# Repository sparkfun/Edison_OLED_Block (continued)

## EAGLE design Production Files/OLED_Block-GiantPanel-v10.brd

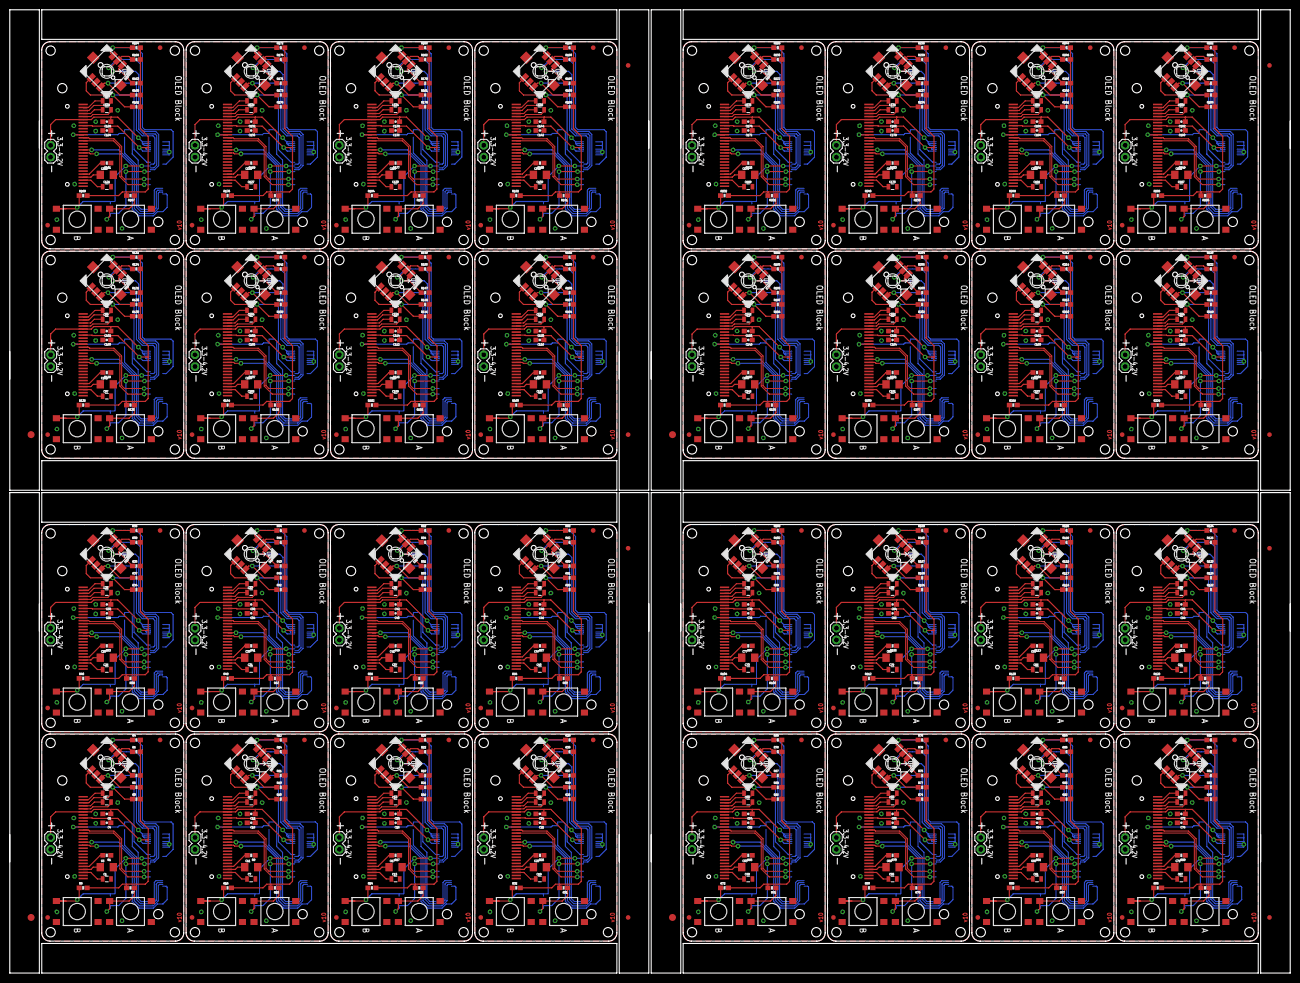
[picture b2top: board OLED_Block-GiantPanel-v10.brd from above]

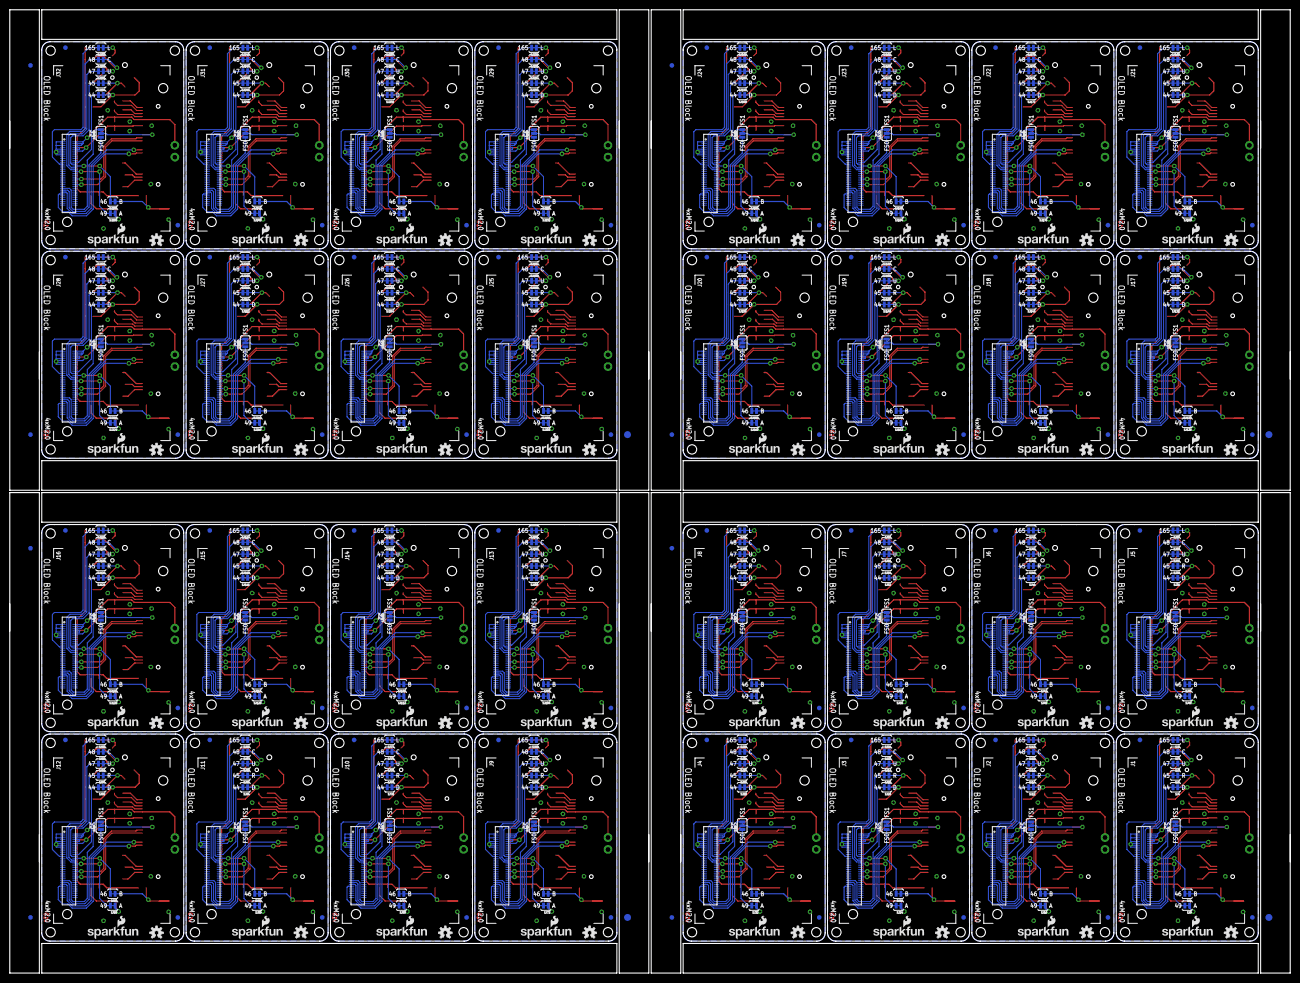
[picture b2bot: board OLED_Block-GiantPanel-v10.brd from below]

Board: 2 copper layers, 274.8 x 206.8 mm, 1112 parts (428 on the bottom side), 1024 nets.

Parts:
C1, C7, C13, C19, C25, C31, C37, C43, C49, C55, C61, C67, C73, C79, C85, C91, C97, C103, C109, C115, C121, C127, C133, C139, C145, C151, C157, C163, C169, C175, C181, C187: 2.2uF; 0805
C2, C3, C8, C9, C14, C15, C20, C21, C26, C27, C32, C33, C38, C39, C44, C45, C50, C51, C56, C57, C62, C63, C68, C69, C74, C75, C80, C81, C86, C87, C92, C93, C98, C99, C104, C105, C110, C111, C116, C117, C122, C123, C128, C129, C134, C135, C140, C141, C146, C147, C152, C153, C158, C159, C164, C165, C170, C171, C176, C177, C182, C183, C188, C189: 1uF X5R; 0805
C4, C6, C10, C12, C16, C18, C22, C24, C28, C30, C34, C36, C40, C42, C46, C48, C52, C54, C58, C60, C64, C66, C70, C72, C76, C78, C82, C84, C88, C90, C94, C96, C100, C102, C106, C108, C112, C114, C118, C120, C124, C126, C130, C132, C136, C138, C142, C144, C148, C150, C154, C156, C160, C162, C166, C168, C172, C174, C178, C180, C184, C186, C190, C192: 1uF; 0603-CAP
C5, C11, C17, C23, C29, C35, C41, C47, C53, C59, C65, C71, C77, C83, C89, C95, C101, C107, C113, C119, C125, C131, C137, C143, C149, C155, C161, C167, C173, C179, C185, C191: 4.7uF/16V; 1206
E$1, E$2, E$9, E$10, E$15, E$16, E$21, E$22: FIDUCIAL-1.5X3
E$3, E$4, E$5, E$6, E$7, E$8, E$11, E$12, E$13, E$14, E$17, E$18, E$19, E$20, E$23, E$24: FIDUCIAL-1X2
FID1, FID2, FID3, FID4, FID5, FID6, FID7, FID8, FID9, FID10, FID11, FID12, FID13, FID14, FID15, FID16, FID17, FID18, FID19, FID20, FID21, FID22, FID23, FID24, FID25, FID26, FID27, FID28, FID29, FID30, FID31, FID32, FID33, FID34, FID35, FID36, FID37, FID38, FID39, FID40, FID41, FID42, FID43, FID44, FID45, FID46, FID47, FID48, FID49, FID50, FID51, FID52, FID53, FID54, FID55, FID56, FID57, FID58, FID59, FID60, FID61, FID62, FID63, FID64, FID65, FID66, FID67, FID68, FID69, FID70, FID71, FID72, FID73, FID74, FID75, FID76, FID77, FID78, FID79, FID80, FID81, FID82, FID83, FID84, FID85, FID86, FID87, FID88, FID89, FID90, FID91, FID92, FID93, FID94, FID95, FID96, FID97, FID98, FID99, FID100, FID101, FID102, FID103, FID104, FID105, FID106, FID107, FID108, FID109, FID110, FID111, FID112, FID113, FID114, FID115, FID116, FID117, FID118, FID119, FID120, FID121, FID122, FID123, FID124, FID125, FID126, FID127, FID128: FIDUCIAL1X2; FIDUCIAL-1X2
J1, J2, J3, J4, J5, J6, J7, J8, J9, J10, J11, J12, J13, J14, J15, J16, J17, J18, J19, J20, J21, J22, J23, J24, J25, J26, J27, J28, J29, J30, J31, J32: EDISON_CONNECTOR_FULLMOUNTING_HOLES; EDISON_DAUGHTER
JP1, JP2, JP3, JP4, JP5, JP6, JP7, JP8, JP9, JP10, JP11, JP12, JP13, JP14, JP15, JP16, JP17, JP18, JP19, JP20, JP21, JP22, JP23, JP24, JP25, JP26, JP27, JP28, JP29, JP30, JP31, JP32: M02PTH; 1X02
LOGO1, LOGO2, LOGO5, LOGO7, LOGO9, LOGO11, LOGO13, LOGO15, LOGO17, LOGO19, LOGO21, LOGO23, LOGO25, LOGO27, LOGO29, LOGO31, LOGO33, LOGO35, LOGO37, LOGO39, LOGO41, LOGO43, LOGO45, LOGO47, LOGO49, LOGO51, LOGO53, LOGO55, LOGO57, LOGO59, LOGO61, LOGO63: OSHW-LOGOS; OSHW-LOGO-S
LOGO3, LOGO4, LOGO6, LOGO8, LOGO10, LOGO12, LOGO14, LOGO16, LOGO18, LOGO20, LOGO22, LOGO24, LOGO26, LOGO28, LOGO30, LOGO32, LOGO34, LOGO36, LOGO38, LOGO40, LOGO42, LOGO44, LOGO46, LOGO48, LOGO50, LOGO52, LOGO54, LOGO56, LOGO58, LOGO60, LOGO62, LOGO64: SFE_LOGO_NAME_FLAME.1_INCH; SFE_LOGO_NAME_FLAME_.1
OLED1, OLED2, OLED3, OLED4, OLED5, OLED6, OLED7, OLED8, OLED9, OLED10, OLED11, OLED12, OLED13, OLED14, OLED15, OLED16, OLED17, OLED18, OLED19, OLED20, OLED21, OLED22, OLED23, OLED24, OLED25, OLED26, OLED27, OLED28, OLED29, OLED30, OLED31, OLED32: OLED0.66; OLED-0.66-64X48
R1, R9, R17, R25, R33, R41, R49, R57, R65, R73, R81, R89, R97, R105, R113, R121, R129, R137, R145, R153, R161, R169, R177, R185, R193, R201, R209, R217, R225, R233, R241, R249: 390k; 0603-RES
R2, R3, R4, R5, R6, R7, R8, R10, R11, R12, R13, R14, R15, R16, R18, R19, R20, R21, R22, R23, R24, R26, R27, R28, R29, R30, R31, R32, R34, R35, R36, R37, R38, R39, R40, R42, R43, R44, R45, R46, R47, R48, R50, R51, R52, R53, R54, R55, R56, R58, R59, R60, R61, R62, R63, R64, R66, R67, R68, R69, R70, R71, R72, R74, R75, R76, R77, R78, R79, R80, R82, R83, R84, R85, R86, R87, R88, R90, R91, R92, R93, R94, R95, R96, R98, R99, R100, R101, R102, R103, R104, R106, R107, R108, R109, R110, R111, R112, R114, R115, R116, R117, R118, R119, R120, R122, R123, R124, R125, R126, R127, R128, R130, R131, R132, R133, R134, R135, R136, R138, R139, R140, R141, R142, R143, R144, R146, R147, R148, R149, R150, R151, R152, R154, R155, R156, R157, R158, R159, R160, R162, R163, R164, R165, R166, R167, R168, R170, R171, R172, R173, R174, R175, R176, R178, R179, R180, R181, R182, R183, R184, R186, R187, R188, R189, R190, R191, R192, R194, R195, R196, R197, R198, R199, R200, R202, R203, R204, R205, R206, R207, R208, R210, R211, R212, R213, R214, R215, R216, R218, R219, R220, R221, R222, R223, R224, R226, R227, R228, R229, R230, R231, R232, R234, R235, R236, R237, R238, R239, R240, R242, R243, R244, R245, R246, R247, R248, R250, R251, R252, R253, R254, R255, R256: 10K; 0603-RES
S1, S4, S7, S10, S13, S16, S19, S22, S25, S28, S31, S34, S37, S40, S43, S46, S49, S52, S55, S58, S61, S64, S67, S70, S73, S76, S79, S82, S85, S88, S91, S94: Button A; TACTILE_SWITCH_TALL
S2, S5, S8, S11, S14, S17, S20, S23, S26, S29, S32, S35, S38, S41, S44, S47, S50, S53, S56, S59, S62, S65, S68, S71, S74, S77, S80, S83, S86, S89, S92, S95: Button B; TACTILE_SWITCH_TALL
S3, S6, S9, S12, S15, S18, S21, S24, S27, S30, S33, S36, S39, S42, S45, S48, S51, S54, S57, S60, S63, S66, S69, S72, S75, S78, S81, S84, S87, S90, S93, S96: JOYSTICK_MINI
SJ1, SJ3, SJ4, SJ5, SJ6, SJ7, SJ8, SJ10, SJ11, SJ12, SJ13, SJ14, SJ15, SJ16, SJ18, SJ19, SJ20, SJ21, SJ22, SJ23, SJ24, SJ26, SJ27, SJ28, SJ29, SJ30, SJ31, SJ32, SJ34, SJ35, SJ36, SJ37, SJ38, SJ39, SJ40, SJ42, SJ43, SJ44, SJ45, SJ46, SJ47, SJ48, SJ50, SJ51, SJ52, SJ53, SJ54, SJ55, SJ56, SJ58, SJ59, SJ60, SJ61, SJ62, SJ63, SJ64, SJ66, SJ67, SJ68, SJ69, SJ70, SJ71, SJ72, SJ74, SJ75, SJ76, SJ77, SJ78, SJ79, SJ80, SJ82, SJ83, SJ84, SJ85, SJ86, SJ87, SJ88, SJ90, SJ91, SJ92, SJ93, SJ94, SJ95, SJ96, SJ98, SJ99, SJ100, SJ101, SJ102, SJ103, SJ104, SJ106, SJ107, SJ108, SJ109, SJ110, SJ111, SJ112, SJ114, SJ115, SJ116, SJ117, SJ118, SJ119, SJ120, SJ122, SJ123, SJ124, SJ125, SJ126, SJ127, SJ128, SJ130, SJ131, SJ132, SJ133, SJ134, SJ135, SJ136, SJ138, SJ139, SJ140, SJ141, SJ142, SJ143, SJ144, SJ146, SJ147, SJ148, SJ149, SJ150, SJ151, SJ152, SJ154, SJ155, SJ156, SJ157, SJ158, SJ159, SJ160, SJ162, SJ163, SJ164, SJ165, SJ166, SJ167, SJ168, SJ170, SJ171, SJ172, SJ173, SJ174, SJ175, SJ176, SJ178, SJ179, SJ180, SJ181, SJ182, SJ183, SJ184, SJ186, SJ187, SJ188, SJ189, SJ190, SJ191, SJ192, SJ194, SJ195, SJ196, SJ197, SJ198, SJ199, SJ200, SJ202, SJ203, SJ204, SJ205, SJ206, SJ207, SJ208, SJ210, SJ211, SJ212, SJ213, SJ214, SJ215, SJ216, SJ218, SJ219, SJ220, SJ221, SJ222, SJ223, SJ224, SJ226, SJ227, SJ228, SJ229, SJ230, SJ231, SJ232, SJ234, SJ235, SJ236, SJ237, SJ238, SJ239, SJ240, SJ242, SJ243, SJ244, SJ245, SJ246, SJ247, SJ248, SJ250, SJ251, SJ252, SJ253, SJ254, SJ255, SJ256: PAD-JUMPER-2-NC_BY_TRACE_YES_SILK
SJ2, SJ9, SJ17, SJ25, SJ33, SJ41, SJ49, SJ57, SJ65, SJ73, SJ81, SJ89, SJ97, SJ105, SJ113, SJ121, SJ129, SJ137, SJ145, SJ153, SJ161, SJ169, SJ177, SJ185, SJ193, SJ201, SJ209, SJ217, SJ225, SJ233, SJ241, SJ249: CS_SEL; PAD-JUMPER-3-2OF3_NC_BY_TRACE_YES_SILK_FULL_BOX

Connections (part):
1.8V: C4.1, J1.12, OLED1.8, R2.2, R3.2, R4.2, R5.2, R6.2, R7.2, R8.2
1.8V1: C10.1, J2.12, OLED2.8, R10.2, R11.2, R12.2, R13.2, R14.2, R15.2, R16.2
1.8V2: C16.1, J3.12, OLED3.8, R18.2, R19.2, R20.2, R21.2, R22.2, R23.2, R24.2
1.8V3: C22.1, J4.12, OLED4.8, R26.2, R27.2, R28.2, R29.2, R30.2, R31.2, R32.2
1.8V4: C28.1, J5.12, OLED5.8, R34.2, R35.2, R36.2, R37.2, R38.2, R39.2, R40.2
1.8V5: C34.1, J6.12, OLED6.8, R42.2, R43.2, R44.2, R45.2, R46.2, R47.2, R48.2
1.8V6: C40.1, J7.12, OLED7.8, R50.2, R51.2, R52.2, R53.2, R54.2, R55.2, R56.2
1.8V7: C46.1, J8.12, OLED8.8, R58.2, R59.2, R60.2, R61.2, R62.2, R63.2, R64.2
1.8V8: C52.1, J9.12, OLED9.8, R66.2, R67.2, R68.2, R69.2, R70.2, R71.2, R72.2
1.8V9: C58.1, J10.12, OLED10.8, R74.2, R75.2, R76.2, R77.2, R78.2, R79.2, R80.2
1.8V10: C64.1, J11.12, OLED11.8, R82.2, R83.2, R84.2, R85.2, R86.2, R87.2, R88.2
1.8V11: C70.1, J12.12, OLED12.8, R90.2, R91.2, R92.2, R93.2, R94.2, R95.2, R96.2
1.8V12: C76.1, J13.12, OLED13.8, R98.2, R99.2, R100.2, R101.2, R102.2, R103.2, R104.2
1.8V13: C82.1, J14.12, OLED14.8, R106.2, R107.2, R108.2, R109.2, R110.2, R111.2, R112.2
1.8V14: C88.1, J15.12, OLED15.8, R114.2, R115.2, R116.2, R117.2, R118.2, R119.2, R120.2
1.8V15: C94.1, J16.12, OLED16.8, R122.2, R123.2, R124.2, R125.2, R126.2, R127.2, R128.2
1.8V16: C100.1, J17.12, OLED17.8, R130.2, R131.2, R132.2, R133.2, R134.2, R135.2, R136.2
1.8V17: C106.1, J18.12, OLED18.8, R138.2, R139.2, R140.2, R141.2, R142.2, R143.2, R144.2
1.8V18: C112.1, J19.12, OLED19.8, R146.2, R147.2, R148.2, R149.2, R150.2, R151.2, R152.2
1.8V19: C118.1, J20.12, OLED20.8, R154.2, R155.2, R156.2, R157.2, R158.2, R159.2, R160.2
1.8V20: C124.1, J21.12, OLED21.8, R162.2, R163.2, R164.2, R165.2, R166.2, R167.2, R168.2
1.8V21: C130.1, J22.12, OLED22.8, R170.2, R171.2, R172.2, R173.2, R174.2, R175.2, R176.2
1.8V22: C136.1, J23.12, OLED23.8, R178.2, R179.2, R180.2, R181.2, R182.2, R183.2, R184.2
1.8V23: C142.1, J24.12, OLED24.8, R186.2, R187.2, R188.2, R189.2, R190.2, R191.2, R192.2
1.8V24: C148.1, J25.12, OLED25.8, R194.2, R195.2, R196.2, R197.2, R198.2, R199.2, R200.2
1.8V25: C154.1, J26.12, OLED26.8, R202.2, R203.2, R204.2, R205.2, R206.2, R207.2, R208.2
1.8V26: C160.1, J27.12, OLED27.8, R210.2, R211.2, R212.2, R213.2, R214.2, R215.2, R216.2
1.8V27: C166.1, J28.12, OLED28.8, R218.2, R219.2, R220.2, R221.2, R222.2, R223.2, R224.2
1.8V28: C172.1, J29.12, OLED29.8, R226.2, R227.2, R228.2, R229.2, R230.2, R231.2, R232.2
1.8V29: C178.1, J30.12, OLED30.8, R234.2, R235.2, R236.2, R237.2, R238.2, R239.2, R240.2
1.8V30: C184.1, J31.12, OLED31.8, R242.2, R243.2, R244.2, R245.2, R246.2, R247.2, R248.2
1.8V31: C190.1, J32.12, OLED32.8, R250.2, R251.2, R252.2, R253.2, R254.2, R255.2, R256.2
3.3V: J1.8, J1.10
3.3V1: J2.8, J2.10
3.3V2: J3.8, J3.10
3.3V3: J4.8, J4.10
3.3V4: J5.8, J5.10
3.3V5: J6.8, J6.10
3.3V6: J7.8, J7.10
3.3V7: J8.8, J8.10
3.3V8: J9.8, J9.10
3.3V9: J10.8, J10.10
3.3V10: J11.8, J11.10
3.3V11: J12.8, J12.10
3.3V12: J13.8, J13.10
3.3V13: J14.8, J14.10
3.3V14: J15.8, J15.10
3.3V15: J16.8, J16.10
3.3V16: J17.8, J17.10
3.3V17: J18.8, J18.10
3.3V18: J19.8, J19.10
3.3V19: J20.8, J20.10
3.3V20: J21.8, J21.10
3.3V21: J22.8, J22.10
3.3V22: J23.8, J23.10
3.3V23: J24.8, J24.10
3.3V24: J25.8, J25.10
3.3V25: J26.8, J26.10
3.3V26: J27.8, J27.10
3.3V27: J28.8, J28.10
3.3V28: J29.8, J29.10
3.3V29: J30.8, J30.10
3.3V30: J31.8, J31.10
3.3V31: J32.8, J32.10
BUT_A: R7.1, S1.A2, SJ8.1
BUT_A1: R15.1, S4.A2, SJ16.1
BUT_A2: R23.1, S7.A2, SJ24.1
BUT_A3: R31.1, S10.A2, SJ32.1
BUT_A4: R39.1, S13.A2, SJ40.1
BUT_A5: R47.1, S16.A2, SJ48.1
BUT_A6: R55.1, S19.A2, SJ56.1
BUT_A7: R63.1, S22.A2, SJ64.1
BUT_A8: R71.1, S25.A2, SJ72.1
BUT_A9: R79.1, S28.A2, SJ80.1
BUT_A10: R87.1, S31.A2, SJ88.1
BUT_A11: R95.1, S34.A2, SJ96.1
BUT_A12: R103.1, S37.A2, SJ104.1
BUT_A13: R111.1, S40.A2, SJ112.1
BUT_A14: R119.1, S43.A2, SJ120.1
BUT_A15: R127.1, S46.A2, SJ128.1
BUT_A16: R135.1, S49.A2, SJ136.1
BUT_A17: R143.1, S52.A2, SJ144.1
BUT_A18: R151.1, S55.A2, SJ152.1
BUT_A19: R159.1, S58.A2, SJ160.1
BUT_A20: R167.1, S61.A2, SJ168.1
BUT_A21: R175.1, S64.A2, SJ176.1
BUT_A22: R183.1, S67.A2, SJ184.1
BUT_A23: R191.1, S70.A2, SJ192.1
BUT_A24: R199.1, S73.A2, SJ200.1
BUT_A25: R207.1, S76.A2, SJ208.1
BUT_A26: R215.1, S79.A2, SJ216.1
BUT_A27: R223.1, S82.A2, SJ224.1
BUT_A28: R231.1, S85.A2, SJ232.1
BUT_A29: R239.1, S88.A2, SJ240.1
BUT_A30: R247.1, S91.A2, SJ248.1
BUT_A31: R255.1, S94.A2, SJ256.1
BUT_B: R8.1, S2.A2, SJ1.1
BUT_B1: R16.1, S5.A2, SJ10.1
BUT_B2: R24.1, S8.A2, SJ18.1
BUT_B3: R32.1, S11.A2, SJ26.1
BUT_B4: R40.1, S14.A2, SJ34.1
BUT_B5: R48.1, S17.A2, SJ42.1
BUT_B6: R56.1, S20.A2, SJ50.1
BUT_B7: R64.1, S23.A2, SJ58.1
BUT_B8: R72.1, S26.A2, SJ66.1
BUT_B9: R80.1, S29.A2, SJ74.1
BUT_B10: R88.1, S32.A2, SJ82.1
BUT_B11: R96.1, S35.A2, SJ90.1
BUT_B12: R104.1, S38.A2, SJ98.1
BUT_B13: R112.1, S41.A2, SJ106.1
BUT_B14: R120.1, S44.A2, SJ114.1
BUT_B15: R128.1, S47.A2, SJ122.1
BUT_B16: R136.1, S50.A2, SJ130.1
BUT_B17: R144.1, S53.A2, SJ138.1
BUT_B18: R152.1, S56.A2, SJ146.1
BUT_B19: R160.1, S59.A2, SJ154.1
BUT_B20: R168.1, S62.A2, SJ162.1
BUT_B21: R176.1, S65.A2, SJ170.1
BUT_B22: R184.1, S68.A2, SJ178.1
BUT_B23: R192.1, S71.A2, SJ186.1
BUT_B24: R200.1, S74.A2, SJ194.1
BUT_B25: R208.1, S77.A2, SJ202.1
BUT_B26: R216.1, S80.A2, SJ210.1
BUT_B27: R224.1, S83.A2, SJ218.1
BUT_B28: R232.1, S86.A2, SJ226.1
BUT_B29: R240.1, S89.A2, SJ234.1
BUT_B30: R248.1, S92.A2, SJ242.1
BUT_B31: R256.1, S95.A2, SJ250.1
C1N: C2.2, OLED1.5
C1N1: C8.2, OLED2.5
C1N2: C14.2, OLED3.5
C1N3: C20.2, OLED4.5
C1N4: C26.2, OLED5.5
C1N5: C32.2, OLED6.5
C1N6: C38.2, OLED7.5
C1N7: C44.2, OLED8.5
C1N8: C50.2, OLED9.5
C1N9: C56.2, OLED10.5
C1N10: C62.2, OLED11.5
C1N11: C68.2, OLED12.5
C1N12: C74.2, OLED13.5
C1N13: C80.2, OLED14.5
C1N14: C86.2, OLED15.5
C1N15: C92.2, OLED16.5
C1N16: C98.2, OLED17.5
C1N17: C104.2, OLED18.5
C1N18: C110.2, OLED19.5
C1N19: C116.2, OLED20.5
C1N20: C122.2, OLED21.5
C1N21: C128.2, OLED22.5
C1N22: C134.2, OLED23.5
C1N23: C140.2, OLED24.5
C1N24: C146.2, OLED25.5
C1N25: C152.2, OLED26.5
C1N26: C158.2, OLED27.5
C1N27: C164.2, OLED28.5
C1N28: C170.2, OLED29.5
C1N29: C176.2, OLED30.5
C1N30: C182.2, OLED31.5
C1N31: C188.2, OLED32.5
C1P: C2.1, OLED1.4
C1P1: C8.1, OLED2.4
C1P2: C14.1, OLED3.4
C1P3: C20.1, OLED4.4
C1P4: C26.1, OLED5.4
C1P5: C32.1, OLED6.4
C1P6: C38.1, OLED7.4
C1P7: C44.1, OLED8.4
C1P8: C50.1, OLED9.4
C1P9: C56.1, OLED10.4
C1P10: C62.1, OLED11.4
C1P11: C68.1, OLED12.4
C1P12: C74.1, OLED13.4
C1P13: C80.1, OLED14.4
C1P14: C86.1, OLED15.4
C1P15: C92.1, OLED16.4
C1P16: C98.1, OLED17.4
C1P17: C104.1, OLED18.4
C1P18: C110.1, OLED19.4
C1P19: C116.1, OLED20.4
C1P20: C122.1, OLED21.4
C1P21: C128.1, OLED22.4
C1P22: C134.1, OLED23.4
C1P23: C140.1, OLED24.4
C1P24: C146.1, OLED25.4
C1P25: C152.1, OLED26.4
C1P26: C158.1, OLED27.4
C1P27: C164.1, OLED28.4
C1P28: C170.1, OLED29.4
C1P29: C176.1, OLED30.4
C1P30: C182.1, OLED31.4
C1P31: C188.1, OLED32.4
C2N: C3.2, OLED1.3
C2N1: C9.2, OLED2.3
C2N2: C15.2, OLED3.3
C2N3: C21.2, OLED4.3
C2N4: C27.2, OLED5.3
C2N5: C33.2, OLED6.3
C2N6: C39.2, OLED7.3
C2N7: C45.2, OLED8.3
C2N8: C51.2, OLED9.3
C2N9: C57.2, OLED10.3
C2N10: C63.2, OLED11.3
C2N11: C69.2, OLED12.3
C2N12: C75.2, OLED13.3
C2N13: C81.2, OLED14.3
C2N14: C87.2, OLED15.3
C2N15: C93.2, OLED16.3
C2N16: C99.2, OLED17.3
C2N17: C105.2, OLED18.3
C2N18: C111.2, OLED19.3
C2N19: C117.2, OLED20.3
C2N20: C123.2, OLED21.3
C2N21: C129.2, OLED22.3
C2N22: C135.2, OLED23.3
C2N23: C141.2, OLED24.3
C2N24: C147.2, OLED25.3
C2N25: C153.2, OLED26.3
C2N26: C159.2, OLED27.3
C2N27: C165.2, OLED28.3
C2N28: C171.2, OLED29.3
C2N29: C177.2, OLED30.3
C2N30: C183.2, OLED31.3
C2N31: C189.2, OLED32.3
C2P: C3.1, OLED1.2
C2P1: C9.1, OLED2.2
C2P2: C15.1, OLED3.2
C2P3: C21.1, OLED4.2
C2P4: C27.1, OLED5.2
C2P5: C33.1, OLED6.2
C2P6: C39.1, OLED7.2
C2P7: C45.1, OLED8.2
C2P8: C51.1, OLED9.2
C2P9: C57.1, OLED10.2
C2P10: C63.1, OLED11.2
C2P11: C69.1, OLED12.2
C2P12: C75.1, OLED13.2
C2P13: C81.1, OLED14.2
C2P14: C87.1, OLED15.2
C2P15: C93.1, OLED16.2
C2P16: C99.1, OLED17.2
C2P17: C105.1, OLED18.2
C2P18: C111.1, OLED19.2
C2P19: C117.1, OLED20.2
C2P20: C123.1, OLED21.2
C2P21: C129.1, OLED22.2
C2P22: C135.1, OLED23.2
C2P23: C141.1, OLED24.2
C2P24: C147.1, OLED25.2
C2P25: C153.1, OLED26.2
C2P26: C159.1, OLED27.2
C2P27: C165.1, OLED28.2
C2P28: C171.1, OLED29.2
C2P29: C177.1, OLED30.2
C2P30: C183.1, OLED31.2
C2P31: C189.1, OLED32.2
GND: C1.2, C4.2, C5.2, C6.2, J1.1, J1.5, J1.9, J1.11, J1.13, J1.15, JP1.1, OLED1.1, OLED1.7, OLED1.9, OLED1.10, OLED1.27, OLED1.28, R1.1, S1.B2, S2.B2, S3.GND
GND1: C7.2, C10.2, C11.2, C12.2, J2.1, J2.5, J2.9, J2.11, J2.13, J2.15, JP2.1, OLED2.1, OLED2.7, OLED2.9, OLED2.10, OLED2.27, OLED2.28, R9.1, S4.B2, S5.B2, S6.GND
GND2: C13.2, C16.2, C17.2, C18.2, J3.1, J3.5, J3.9, J3.11, J3.13, J3.15, JP3.1, OLED3.1, OLED3.7, OLED3.9, OLED3.10, OLED3.27, OLED3.28, R17.1, S7.B2, S8.B2, S9.GND
GND3: C19.2, C22.2, C23.2, C24.2, J4.1, J4.5, J4.9, J4.11, J4.13, J4.15, JP4.1, OLED4.1, OLED4.7, OLED4.9, OLED4.10, OLED4.27, OLED4.28, R25.1, S10.B2, S11.B2, S12.GND
GND4: C25.2, C28.2, C29.2, C30.2, J5.1, J5.5, J5.9, J5.11, J5.13, J5.15, JP5.1, OLED5.1, OLED5.7, OLED5.9, OLED5.10, OLED5.27, OLED5.28, R33.1, S13.B2, S14.B2, S15.GND
GND5: C31.2, C34.2, C35.2, C36.2, J6.1, J6.5, J6.9, J6.11, J6.13, J6.15, JP6.1, OLED6.1, OLED6.7, OLED6.9, OLED6.10, OLED6.27, OLED6.28, R41.1, S16.B2, S17.B2, S18.GND
GND6: C37.2, C40.2, C41.2, C42.2, J7.1, J7.5, J7.9, J7.11, J7.13, J7.15, JP7.1, OLED7.1, OLED7.7, OLED7.9, OLED7.10, OLED7.27, OLED7.28, R49.1, S19.B2, S20.B2, S21.GND
GND7: C43.2, C46.2, C47.2, C48.2, J8.1, J8.5, J8.9, J8.11, J8.13, J8.15, JP8.1, OLED8.1, OLED8.7, OLED8.9, OLED8.10, OLED8.27, OLED8.28, R57.1, S22.B2, S23.B2, S24.GND
GND8: C49.2, C52.2, C53.2, C54.2, J9.1, J9.5, J9.9, J9.11, J9.13, J9.15, JP9.1, OLED9.1, OLED9.7, OLED9.9, OLED9.10, OLED9.27, OLED9.28, R65.1, S25.B2, S26.B2, S27.GND
GND9: C55.2, C58.2, C59.2, C60.2, J10.1, J10.5, J10.9, J10.11, J10.13, J10.15, JP10.1, OLED10.1, OLED10.7, OLED10.9, OLED10.10, OLED10.27, OLED10.28, R73.1, S28.B2, S29.B2, S30.GND
GND10: C61.2, C64.2, C65.2, C66.2, J11.1, J11.5, J11.9, J11.11, J11.13, J11.15, JP11.1, OLED11.1, OLED11.7, OLED11.9, OLED11.10, OLED11.27, OLED11.28, R81.1, S31.B2, S32.B2, S33.GND
GND11: C67.2, C70.2, C71.2, C72.2, J12.1, J12.5, J12.9, J12.11, J12.13, J12.15, JP12.1, OLED12.1, OLED12.7, OLED12.9, OLED12.10, OLED12.27, OLED12.28, R89.1, S34.B2, S35.B2, S36.GND
GND12: C73.2, C76.2, C77.2, C78.2, J13.1, J13.5, J13.9, J13.11, J13.13, J13.15, JP13.1, OLED13.1, OLED13.7, OLED13.9, OLED13.10, OLED13.27, OLED13.28, R97.1, S37.B2, S38.B2, S39.GND
GND13: C79.2, C82.2, C83.2, C84.2, J14.1, J14.5, J14.9, J14.11, J14.13, J14.15, JP14.1, OLED14.1, OLED14.7, OLED14.9, OLED14.10, OLED14.27, OLED14.28, R105.1, S40.B2, S41.B2, S42.GND
GND14: C85.2, C88.2, C89.2, C90.2, J15.1, J15.5, J15.9, J15.11, J15.13, J15.15, JP15.1, OLED15.1, OLED15.7, OLED15.9, OLED15.10, OLED15.27, OLED15.28, R113.1, S43.B2, S44.B2, S45.GND
GND15: C91.2, C94.2, C95.2, C96.2, J16.1, J16.5, J16.9, J16.11, J16.13, J16.15, JP16.1, OLED16.1, OLED16.7, OLED16.9, OLED16.10, OLED16.27, OLED16.28, R121.1, S46.B2, S47.B2, S48.GND
GND16: C97.2, C100.2, C101.2, C102.2, J17.1, J17.5, J17.9, J17.11, J17.13, J17.15, JP17.1, OLED17.1, OLED17.7, OLED17.9, OLED17.10, OLED17.27, OLED17.28, R129.1, S49.B2, S50.B2, S51.GND
GND17: C103.2, C106.2, C107.2, C108.2, J18.1, J18.5, J18.9, J18.11, J18.13, J18.15, JP18.1, OLED18.1, OLED18.7, OLED18.9, OLED18.10, OLED18.27, OLED18.28, R137.1, S52.B2, S53.B2, S54.GND
GND18: C109.2, C112.2, C113.2, C114.2, J19.1, J19.5, J19.9, J19.11, J19.13, J19.15, JP19.1, OLED19.1, OLED19.7, OLED19.9, OLED19.10, OLED19.27, OLED19.28, R145.1, S55.B2, S56.B2, S57.GND
GND19: C115.2, C118.2, C119.2, C120.2, J20.1, J20.5, J20.9, J20.11, J20.13, J20.15, JP20.1, OLED20.1, OLED20.7, OLED20.9, OLED20.10, OLED20.27, OLED20.28, R153.1, S58.B2, S59.B2, S60.GND
GND20: C121.2, C124.2, C125.2, C126.2, J21.1, J21.5, J21.9, J21.11, J21.13, J21.15, JP21.1, OLED21.1, OLED21.7, OLED21.9, OLED21.10, OLED21.27, OLED21.28, R161.1, S61.B2, S62.B2, S63.GND
GND21: C127.2, C130.2, C131.2, C132.2, J22.1, J22.5, J22.9, J22.11, J22.13, J22.15, JP22.1, OLED22.1, OLED22.7, OLED22.9, OLED22.10, OLED22.27, OLED22.28, R169.1, S64.B2, S65.B2, S66.GND
GND22: C133.2, C136.2, C137.2, C138.2, J23.1, J23.5, J23.9, J23.11, J23.13, J23.15, JP23.1, OLED23.1, OLED23.7, OLED23.9, OLED23.10, OLED23.27, OLED23.28, R177.1, S67.B2, S68.B2, S69.GND
GND23: C139.2, C142.2, C143.2, C144.2, J24.1, J24.5, J24.9, J24.11, J24.13, J24.15, JP24.1, OLED24.1, OLED24.7, OLED24.9, OLED24.10, OLED24.27, OLED24.28, R185.1, S70.B2, S71.B2, S72.GND
GND24: C145.2, C148.2, C149.2, C150.2, J25.1, J25.5, J25.9, J25.11, J25.13, J25.15, JP25.1, OLED25.1, OLED25.7, OLED25.9, OLED25.10, OLED25.27, OLED25.28, R193.1, S73.B2, S74.B2, S75.GND
GND25: C151.2, C154.2, C155.2, C156.2, J26.1, J26.5, J26.9, J26.11, J26.13, J26.15, JP26.1, OLED26.1, OLED26.7, OLED26.9, OLED26.10, OLED26.27, OLED26.28, R201.1, S76.B2, S77.B2, S78.GND
GND26: C157.2, C160.2, C161.2, C162.2, J27.1, J27.5, J27.9, J27.11, J27.13, J27.15, JP27.1, OLED27.1, OLED27.7, OLED27.9, OLED27.10, OLED27.27, OLED27.28, R209.1, S79.B2, S80.B2, S81.GND
GND27: C163.2, C166.2, C167.2, C168.2, J28.1, J28.5, J28.9, J28.11, J28.13, J28.15, JP28.1, OLED28.1, OLED28.7, OLED28.9, OLED28.10, OLED28.27, OLED28.28, R217.1, S82.B2, S83.B2, S84.GND
GND28: C169.2, C172.2, C173.2, C174.2, J29.1, J29.5, J29.9, J29.11, J29.13, J29.15, JP29.1, OLED29.1, OLED29.7, OLED29.9, OLED29.10, OLED29.27, OLED29.28, R225.1, S85.B2, S86.B2, S87.GND
GND29: C175.2, C178.2, C179.2, C180.2, J30.1, J30.5, J30.9, J30.11, J30.13, J30.15, JP30.1, OLED30.1, OLED30.7, OLED30.9, OLED30.10, OLED30.27, OLED30.28, R233.1, S88.B2, S89.B2, S90.GND
GND30: C181.2, C184.2, C185.2, C186.2, J31.1, J31.5, J31.9, J31.11, J31.13, J31.15, JP31.1, OLED31.1, OLED31.7, OLED31.9, OLED31.10, OLED31.27, OLED31.28, R241.1, S91.B2, S92.B2, S93.GND
GND31: C187.2, C190.2, C191.2, C192.2, J32.1, J32.5, J32.9, J32.11, J32.13, J32.15, JP32.1, OLED32.1, OLED32.7, OLED32.9, OLED32.10, OLED32.27, OLED32.28, R249.1, S94.B2, S95.B2, S96.GND
GP1: J2.48, OLED2.13
GP2: J2.42, OLED2.12
GP3: J2.34, SJ16.2
GP4: J2.32, SJ15.2
GP5: J2.30, SJ11.2
GP6: J2.28, SJ10.2
GP7: J2.26, SJ14.2
GP8: J2.25, SJ13.2
GP9: J2.24, SJ12.2
GP10: J3.48, OLED3.13
GP11: J3.42, OLED3.12
GP12: J3.34, SJ24.2
GP13: J3.32, SJ23.2
GP14: J1.48, OLED1.13
GP15: J1.42, OLED1.12
GP16: J3.30, SJ19.2
GP17: J3.28, SJ18.2
GP18: J3.26, SJ22.2
GP19: J3.25, SJ21.2
GP20: J3.24, SJ20.2
GP21: J4.48, OLED4.13
GP22: J4.42, OLED4.12
GP23: J4.34, SJ32.2
GP24: J4.32, SJ31.2
GP25: J4.30, SJ27.2
GP26: J4.28, SJ26.2
GP27: J4.26, SJ30.2
GP28: J4.25, SJ29.2
GP29: J4.24, SJ28.2
GP30: J5.48, OLED5.13
GP31: J5.42, OLED5.12
GP32: J5.34, SJ40.2
GP33: J5.32, SJ39.2
GP34: J5.30, SJ35.2
GP35: J5.28, SJ34.2
GP36: J5.26, SJ38.2
GP37: J5.25, SJ37.2
GP38: J5.24, SJ36.2
GP39: J6.48, OLED6.13
GP40: J6.42, OLED6.12
GP41: J6.34, SJ48.2
GP42: J6.32, SJ47.2
GP43: J6.30, SJ43.2
GP44: J1.24, SJ4.2
GP45: J1.26, SJ6.2
GP46: J1.28, SJ1.2
GP47: J1.30, SJ3.2
GP48: J1.32, SJ7.2
GP49: J1.34, SJ8.2
GP50: J6.28, SJ42.2
GP51: J6.26, SJ46.2
GP52: J6.25, SJ45.2
GP53: J6.24, SJ44.2
GP54: J7.48, OLED7.13
GP55: J7.42, OLED7.12
GP56: J7.34, SJ56.2
GP57: J7.32, SJ55.2
GP58: J7.30, SJ51.2
GP59: J7.28, SJ50.2
GP60: J7.26, SJ54.2
GP61: J7.25, SJ53.2
GP62: J7.24, SJ52.2
GP63: J8.48, OLED8.13
GP64: J8.42, OLED8.12
GP65: J8.34, SJ64.2
GP66: J8.32, SJ63.2
GP67: J8.30, SJ59.2
GP68: J8.28, SJ58.2
GP69: J8.26, SJ62.2
GP70: J8.25, SJ61.2
GP71: J8.24, SJ60.2
GP72: J9.48, OLED9.13
GP73: J9.42, OLED9.12
GP74: J9.34, SJ72.2
GP75: J9.32, SJ71.2
GP76: J9.30, SJ67.2
GP77: J9.28, SJ66.2
GP78: J9.26, SJ70.2
GP79: J9.25, SJ69.2
GP80: J9.24, SJ68.2
GP81: J10.48, OLED10.13
GP82: J10.42, OLED10.12
GP83: J10.34, SJ80.2
GP84: J10.32, SJ79.2
GP85: J10.30, SJ75.2
GP86: J10.28, SJ74.2
GP87: J10.26, SJ78.2
GP88: J10.25, SJ77.2
GP89: J10.24, SJ76.2
GP90: J11.48, OLED11.13
GP91: J11.42, OLED11.12
GP92: J11.34, SJ88.2
GP93: J11.32, SJ87.2
GP94: J11.30, SJ83.2
GP95: J11.28, SJ82.2
GP96: J11.26, SJ86.2
GP97: J11.25, SJ85.2
GP98: J11.24, SJ84.2
GP99: J12.48, OLED12.13
GP100: J12.42, OLED12.12
GP101: J12.34, SJ96.2
GP102: J12.32, SJ95.2
GP103: J12.30, SJ91.2
GP104: J12.28, SJ90.2
GP105: J12.26, SJ94.2
GP106: J12.25, SJ93.2
GP107: J12.24, SJ92.2
GP108: J13.48, OLED13.13
GP109: J13.42, OLED13.12
GP109_SPI_2_CLK: J1.55, OLED1.16
GP109_SPI_2_CLK1: J2.55, OLED2.16
GP109_SPI_2_CLK2: J3.55, OLED3.16
GP109_SPI_2_CLK3: J4.55, OLED4.16
GP109_SPI_2_CLK4: J5.55, OLED5.16
GP109_SPI_2_CLK5: J6.55, OLED6.16
GP109_SPI_2_CLK6: J7.55, OLED7.16
GP109_SPI_2_CLK7: J8.55, OLED8.16
GP109_SPI_2_CLK8: J9.55, OLED9.16
GP109_SPI_2_CLK9: J10.55, OLED10.16
GP109_SPI_2_CLK10: J11.55, OLED11.16
GP109_SPI_2_CLK11: J12.55, OLED12.16
GP109_SPI_2_CLK12: J13.55, OLED13.16
GP109_SPI_2_CLK13: J14.55, OLED14.16
GP109_SPI_2_CLK14: J15.55, OLED15.16
GP109_SPI_2_CLK15: J16.55, OLED16.16
GP109_SPI_2_CLK16: J17.55, OLED17.16
GP109_SPI_2_CLK17: J18.55, OLED18.16
GP109_SPI_2_CLK18: J19.55, OLED19.16
GP109_SPI_2_CLK19: J20.55, OLED20.16
GP109_SPI_2_CLK20: J21.55, OLED21.16
GP109_SPI_2_CLK21: J22.55, OLED22.16
GP109_SPI_2_CLK22: J23.55, OLED23.16
GP109_SPI_2_CLK23: J24.55, OLED24.16
GP109_SPI_2_CLK24: J25.55, OLED25.16
GP109_SPI_2_CLK25: J26.55, OLED26.16
GP109_SPI_2_CLK26: J27.55, OLED27.16
GP109_SPI_2_CLK27: J28.55, OLED28.16
GP109_SPI_2_CLK28: J29.55, OLED29.16
GP109_SPI_2_CLK29: J30.55, OLED30.16
GP109_SPI_2_CLK30: J31.55, OLED31.16
GP109_SPI_2_CLK31: J32.55, OLED32.16
GP110: J13.34, SJ104.2
GP110_SPI_2_FS0: J1.53, SJ2.1
GP110_SPI_2_FS1: J2.53, SJ9.1
GP110_SPI_2_FS2: J3.53, SJ17.1
GP110_SPI_2_FS3: J4.53, SJ25.1
GP110_SPI_2_FS4: J5.53, SJ33.1
GP110_SPI_2_FS5: J6.53, SJ41.1
GP110_SPI_2_FS6: J7.53, SJ49.1
GP110_SPI_2_FS7: J8.53, SJ57.1
GP110_SPI_2_FS8: J9.53, SJ65.1
GP110_SPI_2_FS9: J10.53, SJ73.1
GP110_SPI_2_FS10: J11.53, SJ81.1
GP110_SPI_2_FS11: J12.53, SJ89.1
GP110_SPI_2_FS12: J13.53, SJ97.1
GP110_SPI_2_FS13: J14.53, SJ105.1
GP110_SPI_2_FS14: J15.53, SJ113.1
GP110_SPI_2_FS15: J16.53, SJ121.1
GP110_SPI_2_FS16: J17.53, SJ129.1
GP110_SPI_2_FS17: J18.53, SJ137.1
GP110_SPI_2_FS18: J19.53, SJ145.1
GP110_SPI_2_FS19: J20.53, SJ153.1
GP110_SPI_2_FS20: J21.53, SJ161.1
GP110_SPI_2_FS21: J22.53, SJ169.1
GP110_SPI_2_FS22: J23.53, SJ177.1
GP110_SPI_2_FS23: J24.53, SJ185.1
GP110_SPI_2_FS24: J25.53, SJ193.1
GP110_SPI_2_FS25: J26.53, SJ201.1
GP110_SPI_2_FS26: J27.53, SJ209.1
GP110_SPI_2_FS27: J28.53, SJ217.1
GP110_SPI_2_FS28: J29.53, SJ225.1
GP110_SPI_2_FS29: J30.53, SJ233.1
GP110_SPI_2_FS30: J31.53, SJ241.1
GP110_SPI_2_FS31: J32.53, SJ249.1
GP111: J13.32, SJ103.2
GP111_SPI_2_FS1: J1.51, SJ2.3
GP111_SPI_2_FS2: J2.51, SJ9.3
GP111_SPI_2_FS3: J3.51, SJ17.3
GP111_SPI_2_FS4: J4.51, SJ25.3
GP111_SPI_2_FS5: J5.51, SJ33.3
GP111_SPI_2_FS6: J6.51, SJ41.3
GP111_SPI_2_FS7: J7.51, SJ49.3
GP111_SPI_2_FS8: J8.51, SJ57.3
GP111_SPI_2_FS9: J9.51, SJ65.3
GP111_SPI_2_FS10: J10.51, SJ73.3
GP111_SPI_2_FS11: J11.51, SJ81.3
GP111_SPI_2_FS12: J12.51, SJ89.3
GP111_SPI_2_FS13: J13.51, SJ97.3
GP111_SPI_2_FS14: J14.51, SJ105.3
GP111_SPI_2_FS15: J15.51, SJ113.3
GP111_SPI_2_FS16: J16.51, SJ121.3
GP111_SPI_2_FS17: J17.51, SJ129.3
GP111_SPI_2_FS18: J18.51, SJ137.3
GP111_SPI_2_FS19: J19.51, SJ145.3
GP111_SPI_2_FS20: J20.51, SJ153.3
GP111_SPI_2_FS21: J21.51, SJ161.3
GP111_SPI_2_FS22: J22.51, SJ169.3
GP111_SPI_2_FS23: J23.51, SJ177.3
GP111_SPI_2_FS24: J24.51, SJ185.3
GP111_SPI_2_FS25: J25.51, SJ193.3
GP111_SPI_2_FS26: J26.51, SJ201.3
GP111_SPI_2_FS27: J27.51, SJ209.3
GP111_SPI_2_FS28: J28.51, SJ217.3
GP111_SPI_2_FS29: J29.51, SJ225.3
GP111_SPI_2_FS30: J30.51, SJ233.3
GP111_SPI_2_FS31: J31.51, SJ241.3
GP111_SPI_2_FS32: J32.51, SJ249.3
GP112: J13.30, SJ99.2
GP113: J13.28, SJ98.2
GP114: J13.26, SJ102.2
GP115: J13.25, SJ101.2
GP115_SPI_2_TXD: J1.57, OLED1.17
GP115_SPI_2_TXD1: J2.57, OLED2.17
GP115_SPI_2_TXD2: J3.57, OLED3.17
GP115_SPI_2_TXD3: J4.57, OLED4.17
GP115_SPI_2_TXD4: J5.57, OLED5.17
GP115_SPI_2_TXD5: J6.57, OLED6.17
GP115_SPI_2_TXD6: J7.57, OLED7.17
GP115_SPI_2_TXD7: J8.57, OLED8.17
GP115_SPI_2_TXD8: J9.57, OLED9.17
GP115_SPI_2_TXD9: J10.57, OLED10.17
GP115_SPI_2_TXD10: J11.57, OLED11.17
GP115_SPI_2_TXD11: J12.57, OLED12.17
GP115_SPI_2_TXD12: J13.57, OLED13.17
GP115_SPI_2_TXD13: J14.57, OLED14.17
GP115_SPI_2_TXD14: J15.57, OLED15.17
GP115_SPI_2_TXD15: J16.57, OLED16.17
GP115_SPI_2_TXD16: J17.57, OLED17.17
GP115_SPI_2_TXD17: J18.57, OLED18.17
GP115_SPI_2_TXD18: J19.57, OLED19.17
GP115_SPI_2_TXD19: J20.57, OLED20.17
GP115_SPI_2_TXD20: J21.57, OLED21.17
GP115_SPI_2_TXD21: J22.57, OLED22.17
GP115_SPI_2_TXD22: J23.57, OLED23.17
GP115_SPI_2_TXD23: J24.57, OLED24.17
GP115_SPI_2_TXD24: J25.57, OLED25.17
GP115_SPI_2_TXD25: J26.57, OLED26.17
GP115_SPI_2_TXD26: J27.57, OLED27.17
GP115_SPI_2_TXD27: J28.57, OLED28.17
GP115_SPI_2_TXD28: J29.57, OLED29.17
GP115_SPI_2_TXD29: J30.57, OLED30.17
GP115_SPI_2_TXD30: J31.57, OLED31.17
GP115_SPI_2_TXD31: J32.57, OLED32.17
GP116: J13.24, SJ100.2
GP117: J14.48, OLED14.13
GP118: J14.42, OLED14.12
GP119: J14.34, SJ112.2
GP120: J14.32, SJ111.2
GP121: J14.30, SJ107.2
GP122: J14.28, SJ106.2
GP123: J14.26, SJ110.2
GP124: J14.25, SJ109.2
GP125: J14.24, SJ108.2
GP126: J15.48, OLED15.13
GP127: J15.42, OLED15.12
GP128: J15.34, SJ120.2
GP129: J15.32, SJ119.2
GP130: J15.30, SJ115.2
GP131: J15.28, SJ114.2
GP132: J15.26, SJ118.2
GP133: J15.25, SJ117.2
GP134: J15.24, SJ116.2
GP135: J16.48, OLED16.13
GP136: J16.42, OLED16.12
GP137: J16.34, SJ128.2
GP138: J16.32, SJ127.2
GP139: J16.30, SJ123.2
GP140: J16.28, SJ122.2
GP141: J16.26, SJ126.2
GP142: J16.25, SJ125.2
GP143: J16.24, SJ124.2
GP144: J17.48, OLED17.13
GP145: J17.42, OLED17.12
GP146: J17.34, SJ136.2
GP147: J17.32, SJ135.2
GP148: J17.30, SJ131.2
GP149: J17.28, SJ130.2
GP150: J17.26, SJ134.2
GP151: J17.25, SJ133.2
GP152: J17.24, SJ132.2
GP153: J18.48, OLED18.13
GP154: J18.42, OLED18.12
GP155: J18.34, SJ144.2
GP156: J18.32, SJ143.2
GP157: J18.30, SJ139.2
GP158: J18.28, SJ138.2
GP159: J18.26, SJ142.2
GP160: J18.25, SJ141.2
GP161: J18.24, SJ140.2
GP162: J19.48, OLED19.13
GP163: J19.42, OLED19.12
GP164: J19.34, SJ152.2
GP165: J1.25, SJ5.2
GP166: J19.32, SJ151.2
GP167: J19.30, SJ147.2
GP168: J19.28, SJ146.2
GP169: J19.26, SJ150.2
GP170: J19.25, SJ149.2
GP171: J19.24, SJ148.2
GP172: J20.48, OLED20.13
GP173: J20.42, OLED20.12
GP174: J20.34, SJ160.2
GP175: J20.32, SJ159.2
GP176: J20.30, SJ155.2
GP177: J20.28, SJ154.2
GP178: J20.26, SJ158.2
GP179: J20.25, SJ157.2
GP180: J20.24, SJ156.2
GP181: J21.48, OLED21.13
GP182: J21.42, OLED21.12
GP183: J21.34, SJ168.2
GP184: J21.32, SJ167.2
GP185: J21.30, SJ163.2
GP186: J21.28, SJ162.2
GP187: J21.26, SJ166.2
GP188: J21.25, SJ165.2
GP189: J21.24, SJ164.2
GP190: J22.48, OLED22.13
GP191: J22.42, OLED22.12
GP192: J22.34, SJ176.2
GP193: J22.32, SJ175.2
GP194: J22.30, SJ171.2
GP195: J22.28, SJ170.2
GP196: J22.26, SJ174.2
GP197: J22.25, SJ173.2
GP198: J22.24, SJ172.2
GP199: J23.48, OLED23.13
GP200: J23.42, OLED23.12
GP201: J23.34, SJ184.2
GP202: J23.32, SJ183.2
GP203: J23.30, SJ179.2
GP204: J23.28, SJ178.2
GP205: J23.26, SJ182.2
GP206: J23.25, SJ181.2
GP207: J23.24, SJ180.2
GP208: J24.48, OLED24.13
GP209: J24.42, OLED24.12
GP210: J24.34, SJ192.2
GP211: J24.32, SJ191.2
GP212: J24.30, SJ187.2
GP213: J24.28, SJ186.2
GP214: J24.26, SJ190.2
GP215: J24.25, SJ189.2
GP216: J24.24, SJ188.2
GP217: J25.48, OLED25.13
GP218: J25.42, OLED25.12
GP219: J25.34, SJ200.2
GP220: J25.32, SJ199.2
GP221: J25.30, SJ195.2
GP222: J25.28, SJ194.2
GP223: J25.26, SJ198.2
GP224: J25.25, SJ197.2
GP225: J25.24, SJ196.2
GP226: J26.48, OLED26.13
GP227: J26.42, OLED26.12
GP228: J26.34, SJ208.2
GP229: J26.32, SJ207.2
GP230: J26.30, SJ203.2
GP231: J26.28, SJ202.2
GP232: J26.26, SJ206.2
GP233: J26.25, SJ205.2
GP234: J26.24, SJ204.2
GP235: J27.48, OLED27.13
GP236: J27.42, OLED27.12
GP237: J27.34, SJ216.2
GP238: J27.32, SJ215.2
GP239: J27.30, SJ211.2
GP240: J27.28, SJ210.2
GP241: J27.26, SJ214.2
GP242: J27.25, SJ213.2
GP243: J27.24, SJ212.2
GP244: J28.48, OLED28.13
GP245: J28.42, OLED28.12
GP246: J28.34, SJ224.2
GP247: J28.32, SJ223.2
GP248: J28.30, SJ219.2
GP249: J28.28, SJ218.2
GP250: J28.26, SJ222.2
GP251: J28.25, SJ221.2
GP252: J28.24, SJ220.2
GP253: J29.48, OLED29.13
GP254: J29.42, OLED29.12
GP255: J29.34, SJ232.2
GP256: J29.32, SJ231.2
GP257: J29.30, SJ227.2
GP258: J29.28, SJ226.2
GP259: J29.26, SJ230.2
GP260: J29.25, SJ229.2
GP261: J29.24, SJ228.2
GP262: J30.48, OLED30.13
GP263: J30.42, OLED30.12
GP264: J30.34, SJ240.2
GP265: J30.32, SJ239.2
GP266: J30.30, SJ235.2
GP267: J30.28, SJ234.2
GP268: J30.26, SJ238.2
GP269: J30.25, SJ237.2
GP270: J30.24, SJ236.2
GP271: J31.48, OLED31.13
GP272: J31.42, OLED31.12
GP273: J31.34, SJ248.2
GP274: J31.32, SJ247.2
GP275: J31.30, SJ243.2
GP276: J31.28, SJ242.2
GP277: J31.26, SJ246.2
GP278: J31.25, SJ245.2
GP279: J31.24, SJ244.2
GP280: J32.48, OLED32.13
GP281: J32.42, OLED32.12
GP282: J32.34, SJ256.2
GP283: J32.32, SJ255.2
GP284: J32.30, SJ251.2
GP285: J32.28, SJ250.2
GP286: J32.26, SJ254.2
GP287: J32.25, SJ253.2
GP288: J32.24, SJ252.2
IREF: OLED1.24, R1.2
IREF1: OLED2.24, R9.2
IREF2: OLED3.24, R17.2
IREF3: OLED4.24, R25.2
IREF4: OLED5.24, R33.2
IREF5: OLED6.24, R41.2
IREF6: OLED7.24, R49.2
IREF7: OLED8.24, R57.2
IREF8: OLED9.24, R65.2
IREF9: OLED10.24, R73.2
IREF10: OLED11.24, R81.2
IREF11: OLED12.24, R89.2
IREF12: OLED13.24, R97.2
IREF13: OLED14.24, R105.2
IREF14: OLED15.24, R113.2
IREF15: OLED16.24, R121.2
IREF16: OLED17.24, R129.2
IREF17: OLED18.24, R137.2
IREF18: OLED19.24, R145.2
IREF19: OLED20.24, R153.2
IREF20: OLED21.24, R161.2
IREF21: OLED22.24, R169.2
IREF22: OLED23.24, R177.2
IREF23: OLED24.24, R185.2
IREF24: OLED25.24, R193.2
IREF25: OLED26.24, R201.2
IREF26: OLED27.24, R209.2
IREF27: OLED28.24, R217.2
IREF28: OLED29.24, R225.2
IREF29: OLED30.24, R233.2
IREF30: OLED31.24, R241.2
IREF31: OLED32.24, R249.2
JOY_C: R6.1, S3.CTR, SJ7.1
JOY_C1: R14.1, S6.CTR, SJ15.1
JOY_C2: R22.1, S9.CTR, SJ23.1
JOY_C3: R30.1, S12.CTR, SJ31.1
JOY_C4: R38.1, S15.CTR, SJ39.1
JOY_C5: R46.1, S18.CTR, SJ47.1
JOY_C6: R54.1, S21.CTR, SJ55.1
JOY_C7: R62.1, S24.CTR, SJ63.1
JOY_C8: R70.1, S27.CTR, SJ71.1
JOY_C9: R78.1, S30.CTR, SJ79.1
JOY_C10: R86.1, S33.CTR, SJ87.1
JOY_C11: R94.1, S36.CTR, SJ95.1
JOY_C12: R102.1, S39.CTR, SJ103.1
JOY_C13: R110.1, S42.CTR, SJ111.1
JOY_C14: R118.1, S45.CTR, SJ119.1
JOY_C15: R126.1, S48.CTR, SJ127.1
JOY_C16: R134.1, S51.CTR, SJ135.1
JOY_C17: R142.1, S54.CTR, SJ143.1
JOY_C18: R150.1, S57.CTR, SJ151.1
JOY_C19: R158.1, S60.CTR, SJ159.1
JOY_C20: R166.1, S63.CTR, SJ167.1
JOY_C21: R174.1, S66.CTR, SJ175.1
JOY_C22: R182.1, S69.CTR, SJ183.1
JOY_C23: R190.1, S72.CTR, SJ191.1
JOY_C24: R198.1, S75.CTR, SJ199.1
JOY_C25: R206.1, S78.CTR, SJ207.1
JOY_C26: R214.1, S81.CTR, SJ215.1
JOY_C27: R222.1, S84.CTR, SJ223.1
JOY_C28: R230.1, S87.CTR, SJ231.1
JOY_C29: R238.1, S90.CTR, SJ239.1
JOY_C30: R246.1, S93.CTR, SJ247.1
JOY_C31: R254.1, S96.CTR, SJ255.1
JOY_D: R3.1, S3.D, SJ4.1
JOY_D1: R10.1, S6.D, SJ12.1
JOY_D2: R18.1, S9.D, SJ20.1
JOY_D3: R26.1, S12.D, SJ28.1
JOY_D4: R34.1, S15.D, SJ36.1
JOY_D5: R42.1, S18.D, SJ44.1
JOY_D6: R50.1, S21.D, SJ52.1
JOY_D7: R58.1, S24.D, SJ60.1
JOY_D8: R66.1, S27.D, SJ68.1
JOY_D9: R74.1, S30.D, SJ76.1
JOY_D10: R82.1, S33.D, SJ84.1
JOY_D11: R90.1, S36.D, SJ92.1
JOY_D12: R98.1, S39.D, SJ100.1
JOY_D13: R106.1, S42.D, SJ108.1
JOY_D14: R114.1, S45.D, SJ116.1
JOY_D15: R122.1, S48.D, SJ124.1
JOY_D16: R130.1, S51.D, SJ132.1
JOY_D17: R138.1, S54.D, SJ140.1
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
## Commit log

2014-08-06 Initial commit of hardware (v01)
2014-08-06 Removing top-side mezzanine connector
    Rerouting, increasing minimum trace width to 8mil, upping via drills to
    20mil.
2014-08-07 Moving OLED passives to top side
2014-08-08 Moving screen closer towards middle of board
    - Updating Edison package
    - Moving Joystick and buttons towards middle of board.
2014-08-11 adding fiducials to bottom side
2014-08-12 renaming the board
2014-08-12 further genericizing the name
2014-08-20 updating description in the README
2014-09-18 Rename edison_mezzanine_oled.brd to oled_block.brd
2014-09-18 Rename edison_mezzanine_oled.sch to oled_block.sch
2014-09-18 adding pull-up resistors to inputs. v02
2014-09-19 updated SCH edison symbol with new version, moved name to bottom corner of keepout.
2014-09-23 cleaned up pours, added isolate
2014-09-25 file cleanup
2014-10-16 cleaning up some silk (v10)
2014-10-17 Fixing button package. Silk fixes
2014-10-17 updating connector package
2014-10-17 adjusting a few traces
2014-10-17 Ready for reds Added VSYS header No known to-do items
2014-10-23 created v10 panels
2015-01-09 Adding example C++ code and library.
2015-04-01 Updating README and directory file names
2015-07-01 Update gitignore for c++ object files and oled_pong executable
2015-07-01 Remove duplicate constrain position checks
2015-11-20 Update Edison_OLED.h
    Added prototype for printing floats
2015-11-20 Update Edison_OLED.cpp
    Added function for printing floats. Floats are rounded to 2 decimal places
2016-02-15 Changed marco "swap" to "swapOLED"
    I found out the having the macro named "swap" interferes with other system libraries, such as sstream and regex.
2016-02-15 Changed macro "swap" to "swapOLED"
    I found that using the macro name "swap" would interfere with system libraries, such as sstream and regex
2016-03-08 Adding license file, updating README with tutorial links
2017-01-11 nodejs wrapper classes added
2017-01-11 package.json fix
2017-01-13 added nan to preintsll script. added MIT copyright to files
2017-01-20 Command-line tool for Edison OLED Block
2017-01-20 increase wait time 5ms->50ms
2017-01-20 add commands displayoff, displayon
2017-01-20 50ms->10ms
2017-01-20 5ms -> 1ms
2018-02-21 early work on text entry
2018-02-21 makefile
2018-02-21 display
2018-02-21 more spacing
2018-02-21 taller selection box
2018-02-21 draw selected char last
2018-02-21 basic movement
2018-02-21 require multiple clicks
2018-02-21 scrolling after sleeps
2018-02-21 clear the display when done
2018-02-21 text
2018-02-21 output
2018-02-21 clear screen at end
2018-02-21 warnings
2018-02-21 wait 100ms not 1ms
